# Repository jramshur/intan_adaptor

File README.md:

## Description

Adaptor or breakout board for the Intan Technologies RHD2216 electrophysiology interface chip. See Intan's site [here](http://intantech.com/). 

## Contact Info

John T. Ramshur, PhD  
jramshur@gmail.com  
LinkedIn: [http://www.linkedin.com/in/johnramshur](http://www.linkedin.com/in/johnramshur)  
Blog: [http://www.johnramshur.com](http://www.johnramshur.com)

## License

GNU General Public License 3.0

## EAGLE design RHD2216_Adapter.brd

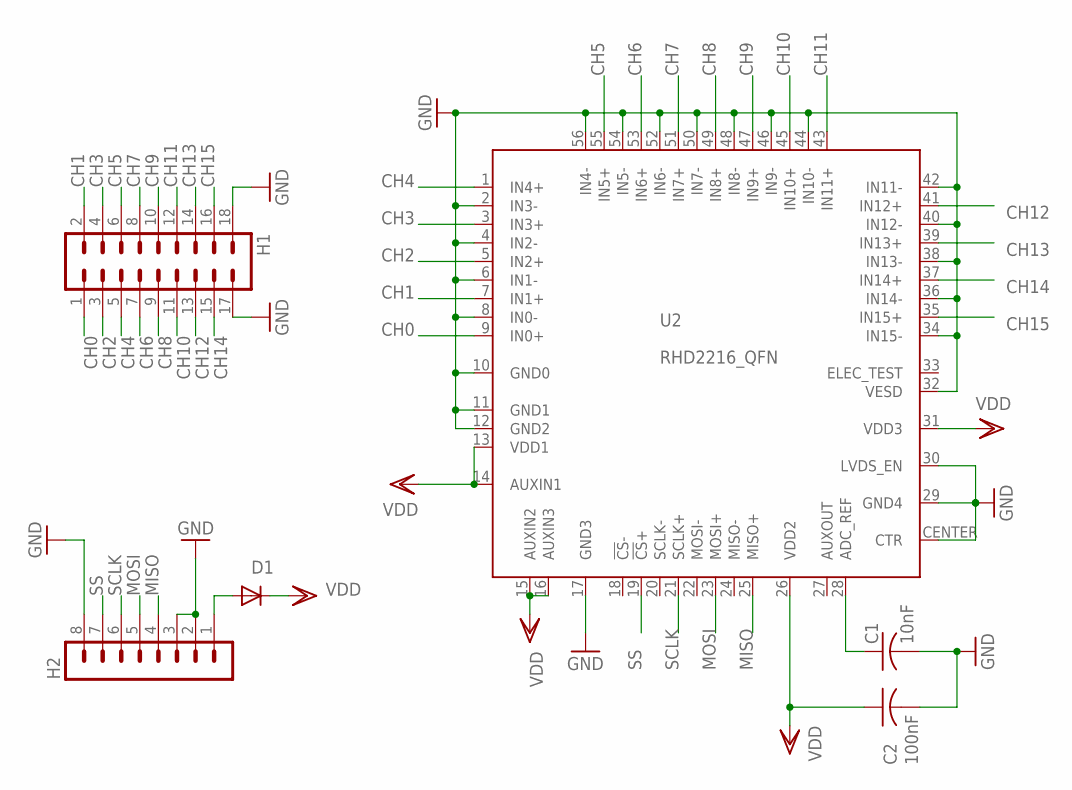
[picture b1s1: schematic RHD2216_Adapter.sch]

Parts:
C1: 10nF; C0402
C2: 100nF; C0402
D1: DIODE-DO214BA; DO214BA
H1: MA09-2W
H2: MA08-1W
U2: RHD2216_QFN; QFN56_8_X_8_LARGE

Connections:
CH0: H1.1, U2.9 (IN0+)
CH1: H1.2, U2.7 (IN1+)
CH2: H1.3, U2.5 (IN2+)
CH3: H1.4, U2.3 (IN3+)
CH4: H1.5, U2.1 (IN4+)
CH5: H1.6, U2.55 (IN5+)
CH6: H1.7, U2.53 (IN6+)
CH7: H1.8, U2.51 (IN7+)
CH8: H1.9, U2.49 (IN8+)
CH9: H1.10, U2.47 (IN9+)
CH10: H1.11, U2.45 (IN10+)
CH11: H1.12, U2.43 (IN11+)
CH12: H1.13, U2.41 (IN12+)
CH13: H1.14, U2.39 (IN13+)
CH14: H1.15, U2.37 (IN14+)
CH15: H1.16, U2.35 (IN15+)
GND: C1.2, C2.2, H1.17, H1.18, H2.2, H2.3, H2.8, U2.2 (IN3-), U2.4 (IN2-), U2.6 (IN1-), U2.8 (IN0-), U2.10 (GND0), U2.11 (GND1), U2.12 (GND2), U2.17 (GND3), U2.29 (GND4), U2.30 (LVDS_EN), U2.32 (VESD), U2.34 (IN15-), U2.36 (IN14-), U2.38 (IN13-), U2.40 (IN12-), U2.42 (IN11-), U2.44 (IN10-), U2.46 (IN9-), U2.48 (IN8-), U2.50 (IN7-), U2.52 (IN6-), U2.54 (IN5-), U2.56 (IN4-), U2.CENTER (CTR)
MISO: H2.4, U2.25 (MISO+)
MOSI: H2.5, U2.23 (MOSI+)
unnamed: D1.A, H2.1
unnamed: C1.1, U2.28 (ADC_REF)
SCLK: H2.6, U2.21 (SCLK+)
SS: H2.7, U2.19 (!CS!+)
VDD: C2.1, D1.C, U2.13 (VDD1), U2.14 (AUXIN1), U2.15 (AUXIN2), U2.16 (AUXIN3), U2.26 (VDD2), U2.31 (VDD3)

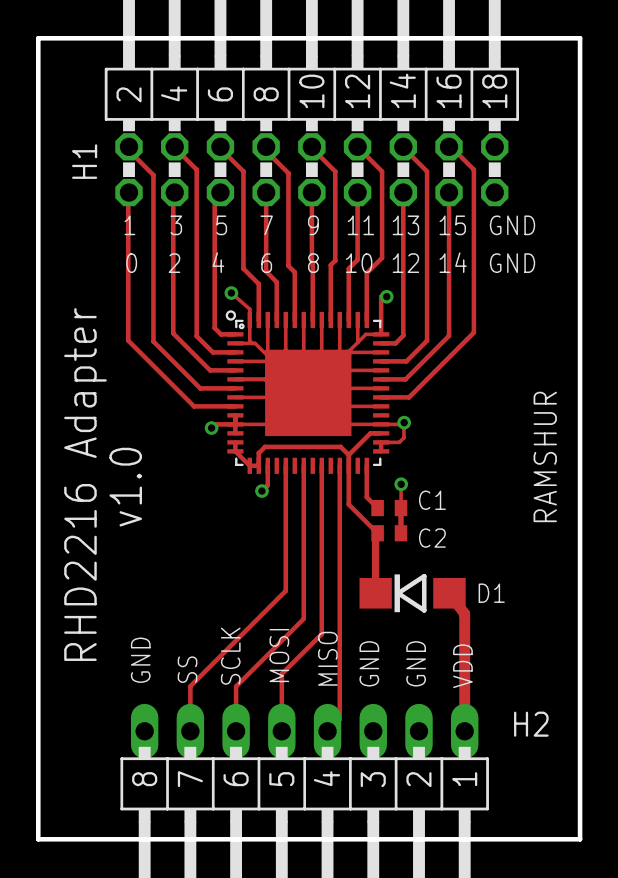
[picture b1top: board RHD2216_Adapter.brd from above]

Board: 2 copper layers, 30.1 x 44.5 mm, 6 parts (0 on the bottom side), 24 nets.

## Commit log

2015-09-15 :space_invader: Added .gitattributes & .gitignore files
